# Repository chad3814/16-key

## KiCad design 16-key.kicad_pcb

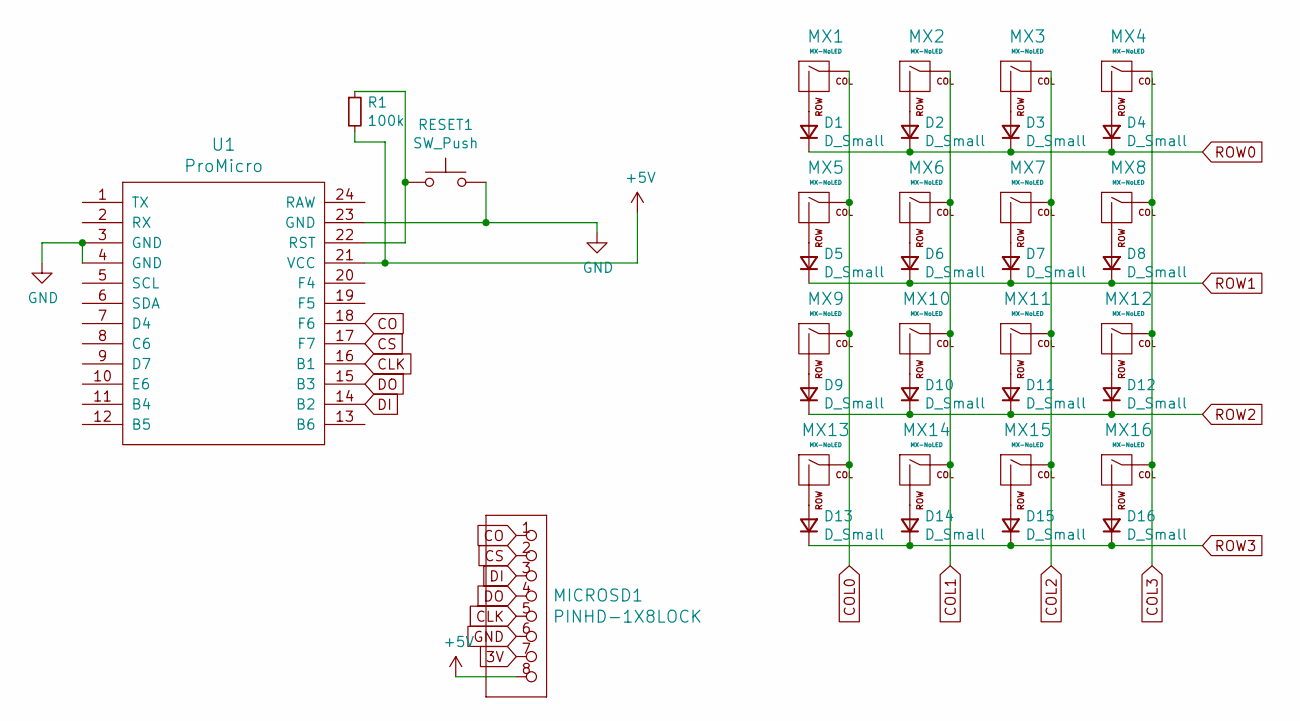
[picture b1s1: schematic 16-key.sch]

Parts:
D1, D2, D3, D4, D5, D6, D7, D8, D9, D10, D11, D12, D13, D14, D15, D16: D_Small; D_0805_2012Metric
MICROSD1: PINHD-1X8LOCK; PinHeader_1x08_P1.00mm_Vertical
MX1, MX2, MX3, MX4, MX5, MX6, MX7, MX8, MX9, MX10, MX11, MX12, MX13, MX14, MX15, MX16: MX-NoLED; MXOnly-1U-NoLED
R1: 100k; R_0805_2012Metric
RESET1: SW_Push; SW_PUSH_6mm
U1: ProMicro

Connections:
3V: MICROSD1.7
+5V: MICROSD1.8, R1.2, U1.21 (VCC)
CLK: MICROSD1.5, U1.16 (B1)
CO: MICROSD1.1, U1.18 (F6)
COL0: MX1.1 (COL), MX5.1 (COL), MX9.1 (COL), MX13.1 (COL)
COL1: MX2.1 (COL), MX6.1 (COL), MX10.1 (COL), MX14.1 (COL)
COL2: MX3.1 (COL), MX7.1 (COL), MX11.1 (COL), MX15.1 (COL)
COL3: MX4.1 (COL), MX8.1 (COL), MX12.1 (COL), MX16.1 (COL)
CS: MICROSD1.2, U1.17 (F7)
DI: MICROSD1.3, U1.14 (B2)
DO: MICROSD1.4, U1.15 (B3)
GND: MICROSD1.6, RESET1.2, U1.3 (GND), U1.4 (GND), U1.23 (GND)
unnamed: D1.2 (A), MX1.2 (ROW)
unnamed: D2.2 (A), MX2.2 (ROW)
unnamed: D3.2 (A), MX3.2 (ROW)
unnamed: D4.2 (A), MX4.2 (ROW)
unnamed: D5.2 (A), MX5.2 (ROW)
unnamed: D6.2 (A), MX6.2 (ROW)
unnamed: D7.2 (A), MX7.2 (ROW)
unnamed: D8.2 (A), MX8.2 (ROW)
unnamed: D9.2 (A), MX9.2 (ROW)
unnamed: D10.2 (A), MX10.2 (ROW)
unnamed: D11.2 (A), MX11.2 (ROW)
unnamed: D12.2 (A), MX12.2 (ROW)
unnamed: D13.2 (A), MX13.2 (ROW)
unnamed: D14.2 (A), MX14.2 (ROW)
unnamed: D15.2 (A), MX15.2 (ROW)
unnamed: D16.2 (A), MX16.2 (ROW)
unnamed: R1.1, RESET1.1, U1.22 (RST)
ROW0: D1.1 (K), D2.1 (K), D3.1 (K), D4.1 (K)
ROW1: D5.1 (K), D6.1 (K), D7.1 (K), D8.1 (K)
ROW2: D9.1 (K), D10.1 (K), D11.1 (K), D12.1 (K)
ROW3: D13.1 (K), D14.1 (K), D15.1 (K), D16.1 (K)

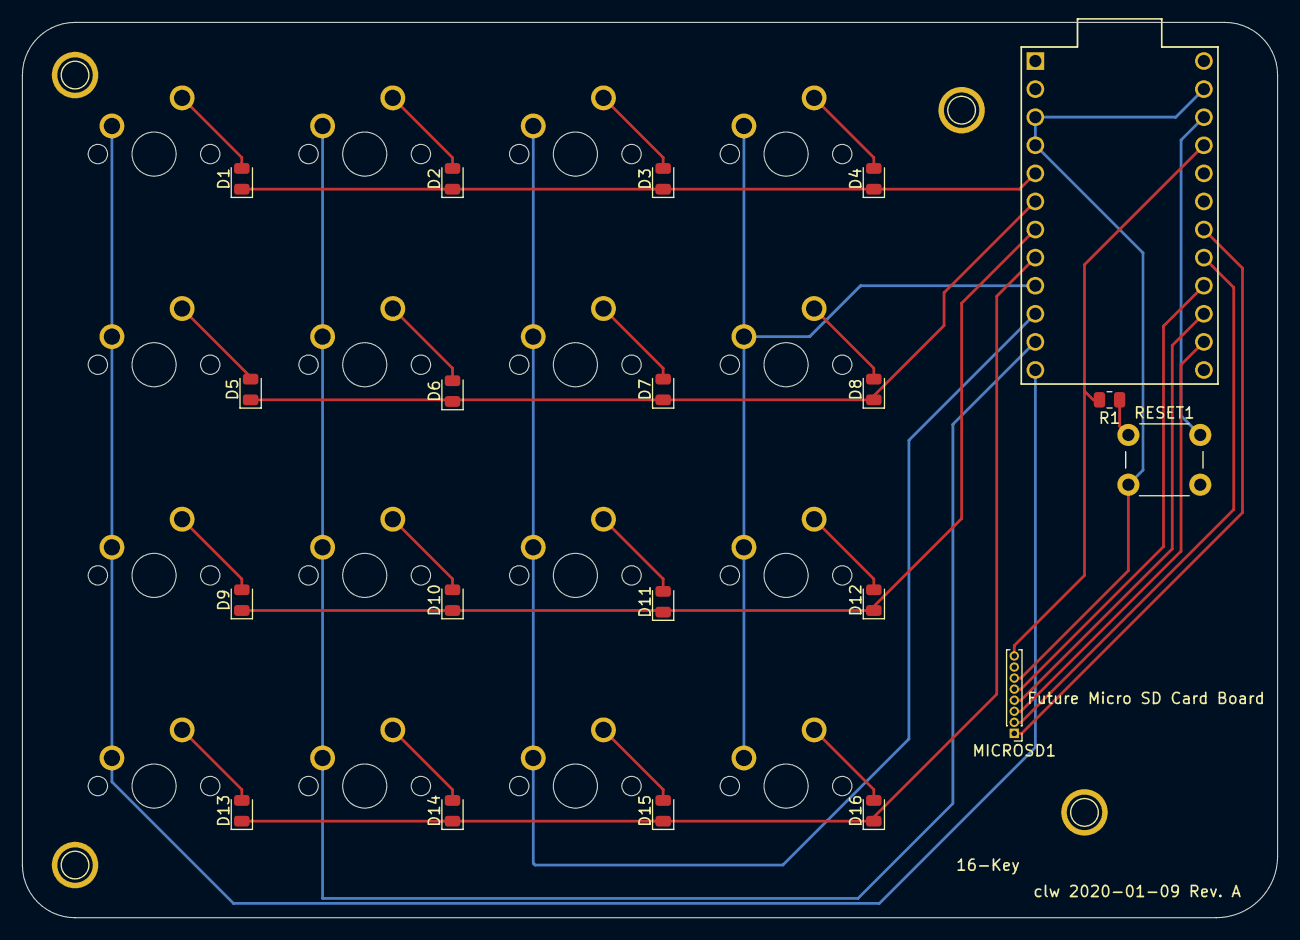
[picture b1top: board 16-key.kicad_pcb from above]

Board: 2 copper layers, 113.5 x 81.0 mm, 36 parts (0 on the bottom side), 32 nets.

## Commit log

2021-01-09 progress
2021-01-09 basically done
2021-01-09 added pull up resistor
2021-01-09 generated gerb files
2021-01-09 moved lettering to silk screen
2021-01-09 added mounting holes
